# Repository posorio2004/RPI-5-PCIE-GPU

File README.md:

# RPI-5-PCIE-GPU
Documentation of my work in getting an MSI Rx 580 to work on a Raspberry Pi 5

# Things I've completed:
1. Designed and manufactured a PCIE x16 adapter for the RPI 5
  - This is still being debugged currently. My adapter seems to work for an geforce 8600gt yet not the RX 580 unless I use a mining adapter which is odd. This is being investigated.
  - Initially used a generic 16 pin fpc cable however this resulted in an unstable connection. As a result I upgraded to [this](https://shop.pimoroni.com/products/pcie-flex-cable-for-nvme-base-and-raspberry-pi-5?variant=41449370910803) cable but it requried modifications to both my board (installing the fpc connector backwards) and to the cable itself (cutting off the extra two unneeded connectors). 
  - I initially tried to make the PC PSU turn on automatically however I was unsuccessful in doing so. I ended up shorting the two required pins to force the PSU to always be on.

2. Designed a basic stand for the PI and the RX 580. This stand was created to support my PCB temporarily, as I would have to recreate it once I fix the problems with the PCB.

# Tasks:

1. Hardware:
   - Creating an updated version of the board once I can fix/debug all problems with my current design
   
2. Software:
  - Installing Drivers
  - Running Programs to test functionality. (Box86/64)

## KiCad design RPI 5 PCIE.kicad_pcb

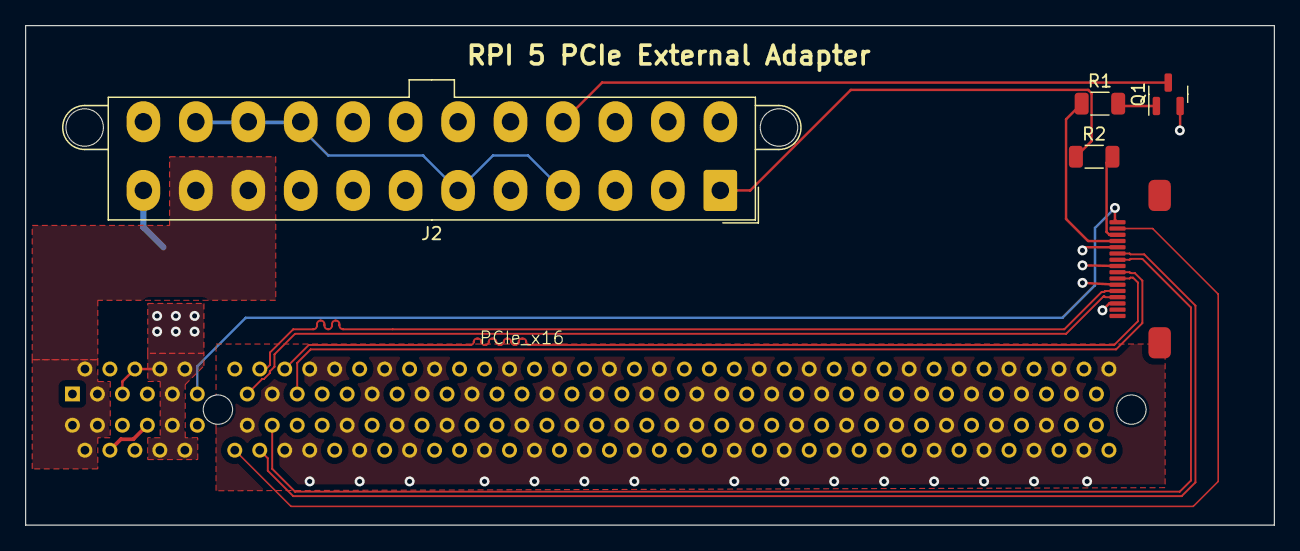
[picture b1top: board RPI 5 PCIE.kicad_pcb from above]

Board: 4 copper layers, 100.0 x 40.0 mm, 6 parts (0 on the bottom side), 15 nets.

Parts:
J1: Conn_01x16; Cvilux_CF31161D0R0-05-NH
J2: ATX-24; Molex_Mini-Fit_Jr_5566-24A2_2x12_P4.20mm_Vertical
PCIe_x16: PCIe x16
Q1: MMBT3904; SOT-23
R1: 4.7k; R_1206_3216Metric
R2: 2.2k; R_1206_3216Metric

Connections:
+3.3V: J2.1 (+3.3V), J2.2 (+3.3V), J2.12 (+3.3V), J2.13 (+3.3V), PCIe_x16.A5, PCIe_x16.A6, PCIe_x16.A8, PCIe_x16.A9, PCIe_x16.A10, PCIe_x16.B8, PCIe_x16.B9, PCIe_x16.B10, R2.1
+12V: J2.10 (+12V), J2.11 (+12V), PCIe_x16.A2, PCIe_x16.A3, PCIe_x16.B1, PCIe_x16.B2, PCIe_x16.B3
/PCIE_CLKREQ_N: J1.15, PCIe_x16.B12
/PCIE_CLK_N: J1.5, PCIe_x16.A14
/PCIE_CLK_P: J1.4, PCIe_x16.A13
/PCIE_RST_B: J1.16, PCIe_x16.A11
/PCIE_RX_N: J1.8, PCIe_x16.A17
/PCIE_RX_P: J1.7, PCIe_x16.A16
/PCIE_TX_N: J1.10, PCIe_x16.B15
/PCIE_TX_P: J1.11, PCIe_x16.B14
GND: J1.3, J1.6, J1.9, J1.12, J2.3 (GND), J2.5 (GND), J2.7 (GND), J2.15 (GND), J2.17 (GND), J2.18 (GND), J2.19 (GND), J2.24 (GND), PCIe_x16.A4, PCIe_x16.A15, PCIe_x16.A18, PCIe_x16.A20, PCIe_x16.A23, PCIe_x16.A24, PCIe_x16.A27, PCIe_x16.A28, PCIe_x16.A31, PCIe_x16.A34, PCIe_x16.A37, PCIe_x16.A38, PCIe_x16.A41, PCIe_x16.A42, PCIe_x16.A45, PCIe_x16.A46, PCIe_x16.A49, PCIe_x16.A51, PCIe_x16.A54, PCIe_x16.A55, PCIe_x16.A58, PCIe_x16.A59, PCIe_x16.A62, PCIe_x16.A63, PCIe_x16.A66, PCIe_x16.A67, PCIe_x16.A70, PCIe_x16.A71, PCIe_x16.A74, PCIe_x16.A75, PCIe_x16.A78, PCIe_x16.A79, PCIe_x16.A82, PCIe_x16.B4, PCIe_x16.B7, PCIe_x16.B13, PCIe_x16.B16, PCIe_x16.B18, PCIe_x16.B21, PCIe_x16.B22, PCIe_x16.B25, PCIe_x16.B26, PCIe_x16.B29, PCIe_x16.B32, PCIe_x16.B35, PCIe_x16.B36, PCIe_x16.B39, PCIe_x16.B40, PCIe_x16.B43, PCIe_x16.B44, PCIe_x16.B47, PCIe_x16.B49, PCIe_x16.B52, PCIe_x16.B53, PCIe_x16.B56, PCIe_x16.B57, PCIe_x16.B60, PCIe_x16.B61, PCIe_x16.B64, PCIe_x16.B65, PCIe_x16.B68, PCIe_x16.B69, PCIe_x16.B72, PCIe_x16.B73, PCIe_x16.B76, PCIe_x16.B77, PCIe_x16.B80, Q1.2 (E)
unnamed: J1.13, R1.1
unnamed: J1.14, R2.2
unnamed: J2.16 (PS_ON#), Q1.3 (C)
unnamed: Q1.1 (B), R1.2

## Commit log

2024-01-13 Uploaded Empty Project Files
2024-01-13 Created Schematic
2024-01-13 Started PCB
2024-01-14 Attempted PCB Design
    Realized that a 4-layer PCB is required. Will continue research into impedance controlled PCBs
2024-01-14 Updated PCB to 4-layer Board
2024-01-14 Small PCB updates
2024-01-15 Updated Tracer Width to JLCPCB recommendations
2024-01-19 Finished PCB v1
    This was the first prototype to be sent to JLC PCB
2024-04-30 Added 3d support models
2024-04-30 Fixed Pi Base Model
